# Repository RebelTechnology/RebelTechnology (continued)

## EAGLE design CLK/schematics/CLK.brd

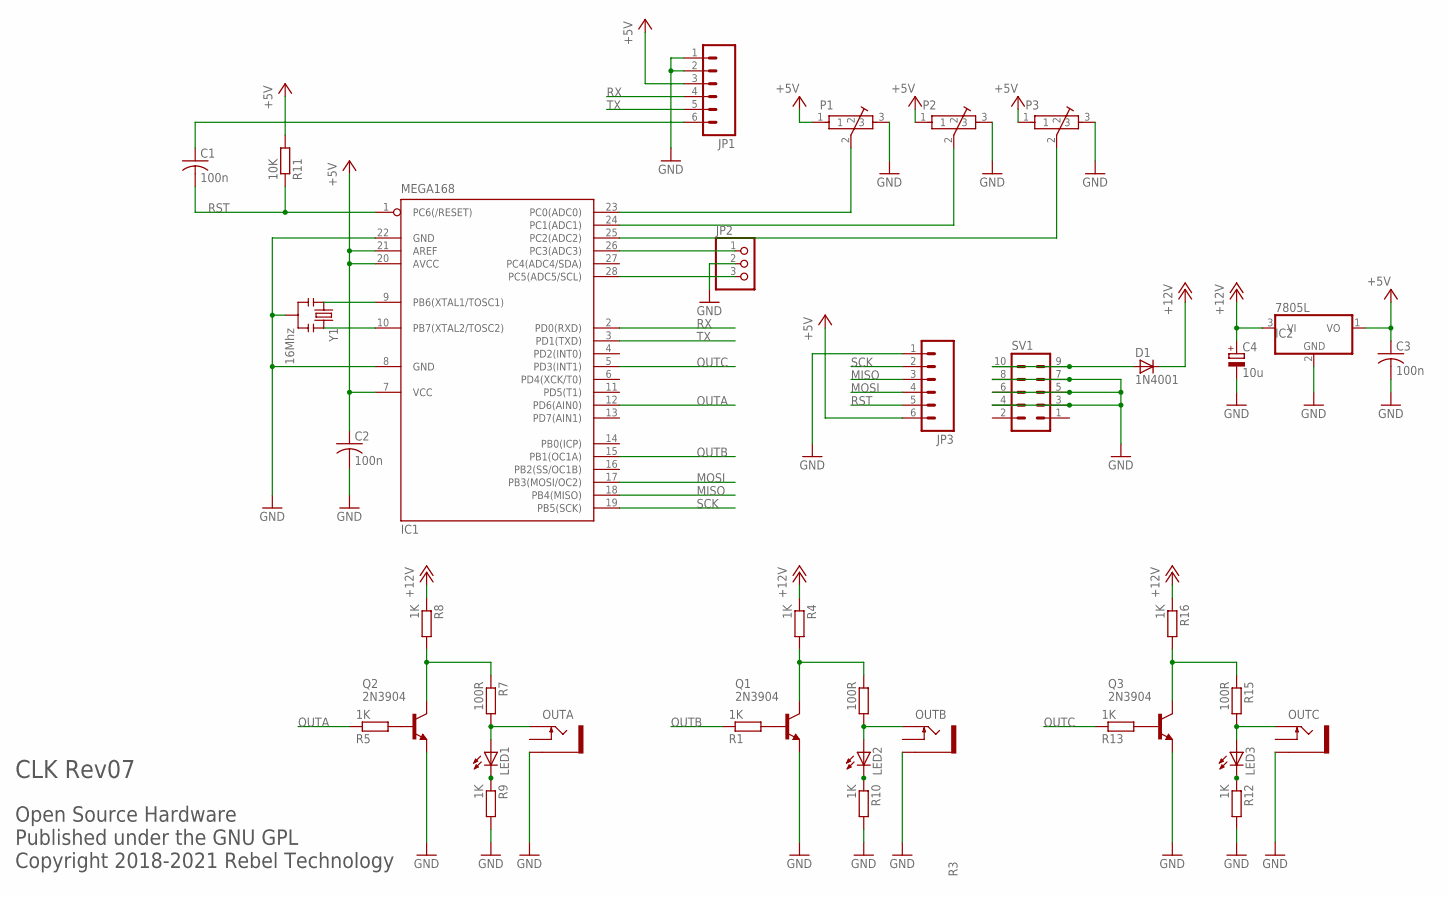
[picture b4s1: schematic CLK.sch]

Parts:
C1, C2, C3: 100n; C050-024X044
C4: 10u; E5-6
D1: 1N4001; DIODE-1N4001
IC1: MEGA168; DIL28-3
IC2: 7805L; TO92
JP1, JP3: M06SIP; 1X06
JP2: PINHD-1X3; 1X03
LED1, LED2, LED3: LED3MM
OUTA: PJ302M
OUTB: PJ302M
OUTC: PJ302M
P1, P2, P3: POT-BOURNS-PTD901
Q1, Q2, Q3: 2N3904; TO92
R1, R4, R5, R8, R9, R10, R12, R13, R16: 1K; 0204/7
R3, R7, R15: 100R; 0204/7
R11: 10K; 0204/7
SV1: MA05-2
Y1: 16Mhz; RESONATOR-PTH

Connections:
+5V: C2.1, C3.1, IC1.7 (VCC), IC1.20 (AVCC), IC1.21 (AREF), IC2.1 (VO), JP1.3, JP3.6, P1.1, P2.1, P3.1, R11.2
+12V: C4.+, D1.C, IC2.3 (VI), R4.1, R8.1, R16.1
ADC0: IC1.23 (PC0(ADC0)), P1.2
ADC1: IC1.24 (PC1(ADC1)), P2.2
ADC2: IC1.25 (PC2(ADC2)), P3.2
GND: C2.2, C3.2, C4.-, IC1.8 (GND), IC1.22 (GND), IC2.2 (GND), JP1.1, JP1.2, JP2.2, JP3.1, OUTA.GND (SLEEVE), OUTB.GND (SLEEVE), OUTC.GND (SLEEVE), P1.3, P2.3, P3.3, Q1.3 (E), Q2.3 (E), Q3.3 (E), R9.2, R10.2, R12.2, SV1.3, SV1.4, SV1.5, SV1.6, SV1.7, SV1.8, Y1.2
MISO: IC1.18 (PB4(MISO)), JP3.3
MOSI: IC1.17 (PB3(MOSI/OC2)), JP3.4
unnamed: LED3.K (C), R12.1
unnamed: IC1.9 (PB6(XTAL1/TOSC1)), Y1.1
unnamed: IC1.10 (PB7(XTAL2/TOSC2)), Y1.3
unnamed: IC1.28 (PC5(ADC5/SCL)), JP2.3
unnamed: LED2.A, OUTB.TIP, R3.2
unnamed: Q1.1 (C), R3.1, R4.2
unnamed: IC1.26 (PC3(ADC3)), JP2.1
unnamed: Q1.2 (B), R1.2
unnamed: Q3.2 (B), R13.2
unnamed: LED3.A, OUTC.TIP, R15.2
unnamed: Q3.1 (C), R15.1, R16.2
unnamed: Q2.2 (B), R5.2
unnamed: LED1.A, OUTA.TIP, R7.2
unnamed: Q2.1 (C), R7.1, R8.2
unnamed: LED1.K (C), R9.1
unnamed: C1.1, JP1.6
unnamed: LED2.K (C), R10.1
unnamed: D1.A, SV1.9, SV1.10
OUTA: IC1.12 (PD6(AIN0)), R5.1
OUTB: IC1.15 (PB1(OC1A)), R1.1
OUTC: IC1.5 (PD3(INT1)), R13.1
RST: C1.2, IC1.1 (PC6(/RESET)), JP3.5, R11.1
RX: IC1.2 (PD0(RXD)), JP1.4
SCK: IC1.19 (PB5(SCK)), JP3.2
TX: IC1.3 (PD1(TXD)), JP1.5

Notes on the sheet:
Open Source Hardware Published under the GNU GPL Copyright 2018-2021 Rebel Technology
CLK Rev07

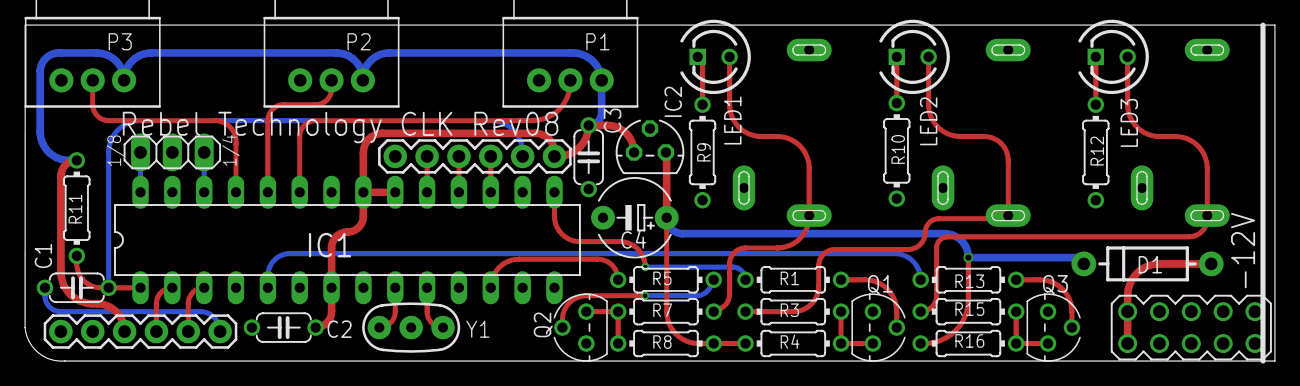
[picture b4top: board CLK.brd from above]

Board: 2 copper layers, 99.7 x 26.8 mm, 37 parts (0 on the bottom side), 33 nets.

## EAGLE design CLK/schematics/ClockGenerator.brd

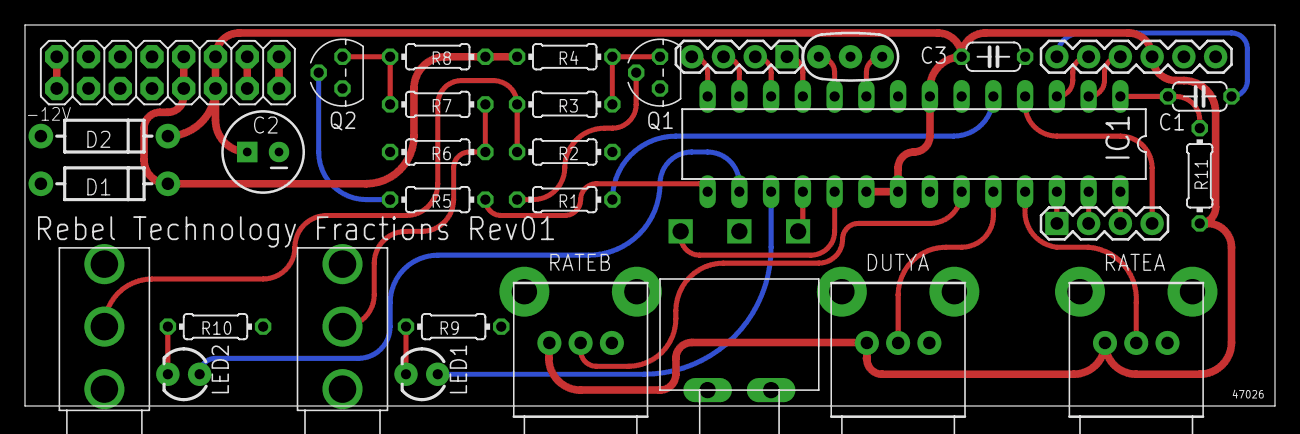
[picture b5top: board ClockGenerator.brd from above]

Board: 2 copper layers, 100.0 x 30.5 mm, 32 parts (0 on the bottom side), 37 nets.

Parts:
C1, C3: 100n; C050-024X044
C2: 100u; CPOL-RADIAL-100UF-25V
D1, D2: DIODE-1N4001
DUTYA: POT-ALPS_RK09L; POT-ALPS_RK09L1120
IC1: MEGA168; DIL28-3
JP1: 1X06
JP2, JP3: 1X04
LED1, LED2: LED3MM
OUTA: JACK-UJ-3502-R; UJ-3502-R
OUTB: JACK-UJ-3502-R; UJ-3502-R
Q1, Q2: 2N3904; TO92
R1, R2, R4, R5, R6, R8, R9, R10: 1K; 0204/7
R3, R7: 100; 0204/7
R11: 10K; 0204/7
RATEA: POT-ALPS_RK09L; POT-ALPS_RK09L1120
RATEB: POT-ALPS_RK09L; POT-ALPS_RK09L1120
SW1: SWITCH-TOGGLE; SWITCH-SPDT-SALECOM-T8020
U$2: M08X2; 2X8
Y1: 16Mhz; RESONATOR-PTH

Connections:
+5V: C2.1, C3.1, D2.C, DUTYA.1, IC1.7, IC1.20, IC1.21, JP1.3, R11.2, RATEA.1, RATEB.1, U$2.11, U$2.12
+12V: D1.C, R4.1, R8.1, U$2.9, U$2.10
ADC0: IC1.23, RATEB.2
ADC1: DUTYA.2, IC1.24
ADC2: IC1.25, RATEA.2
GND: C2.2, C3.2, D1.A, D2.A, DUTYA.3, DUTYA.SHLD1, DUTYA.SHLD2, IC1.8, IC1.22, JP1.1, JP1.2, OUTA.P$3, OUTB.P$3, Q1.3, Q2.3, R2.1, R6.1, R9.2, R10.2, RATEA.3, RATEA.SHLD1, RATEA.SHLD2, RATEB.3, RATEB.SHLD1, RATEB.SHLD2, SW1.2, U$2.3, U$2.4, U$2.5, U$2.6, U$2.7, U$2.8, Y1.2
unnamed: IC1.19, SW1.1
unnamed: IC1.11, JP2.1
unnamed: IC1.16, LED2.A
unnamed: IC1.9, Y1.1
unnamed: IC1.10, Y1.3
unnamed: IC1.17, LED1.A
unnamed: IC1.4, JP3.4
unnamed: IC1.28, JP3.3
unnamed: IC1.27, JP3.2
unnamed: OUTB.P$1, R2.2, R3.2
unnamed: Q1.1, R3.1, R4.2
unnamed: IC1.26, JP3.1
unnamed: IC1.12, JP2.2
unnamed: IC1.13, JP2.3
unnamed: U$2.13, U$2.14
unnamed: IC1.14, JP2.4
unnamed: IC1.18, SW1.3
unnamed: Q1.2, R1.2
unnamed: Q2.2, R5.2
unnamed: OUTA.P$1, R6.2, R7.2
unnamed: Q2.1, R7.1, R8.2
unnamed: LED1.K, R9.1
unnamed: C1.1, JP1.6
unnamed: LED2.K, R10.1
unnamed: C1.2, IC1.1, R11.1
OUTA: IC1.15, R5.1
OUTB: IC1.5, R1.1
PWR_BUS: U$2.15, U$2.16
RX: IC1.2, JP1.4
TX: IC1.3, JP1.5
V-: U$2.1, U$2.2

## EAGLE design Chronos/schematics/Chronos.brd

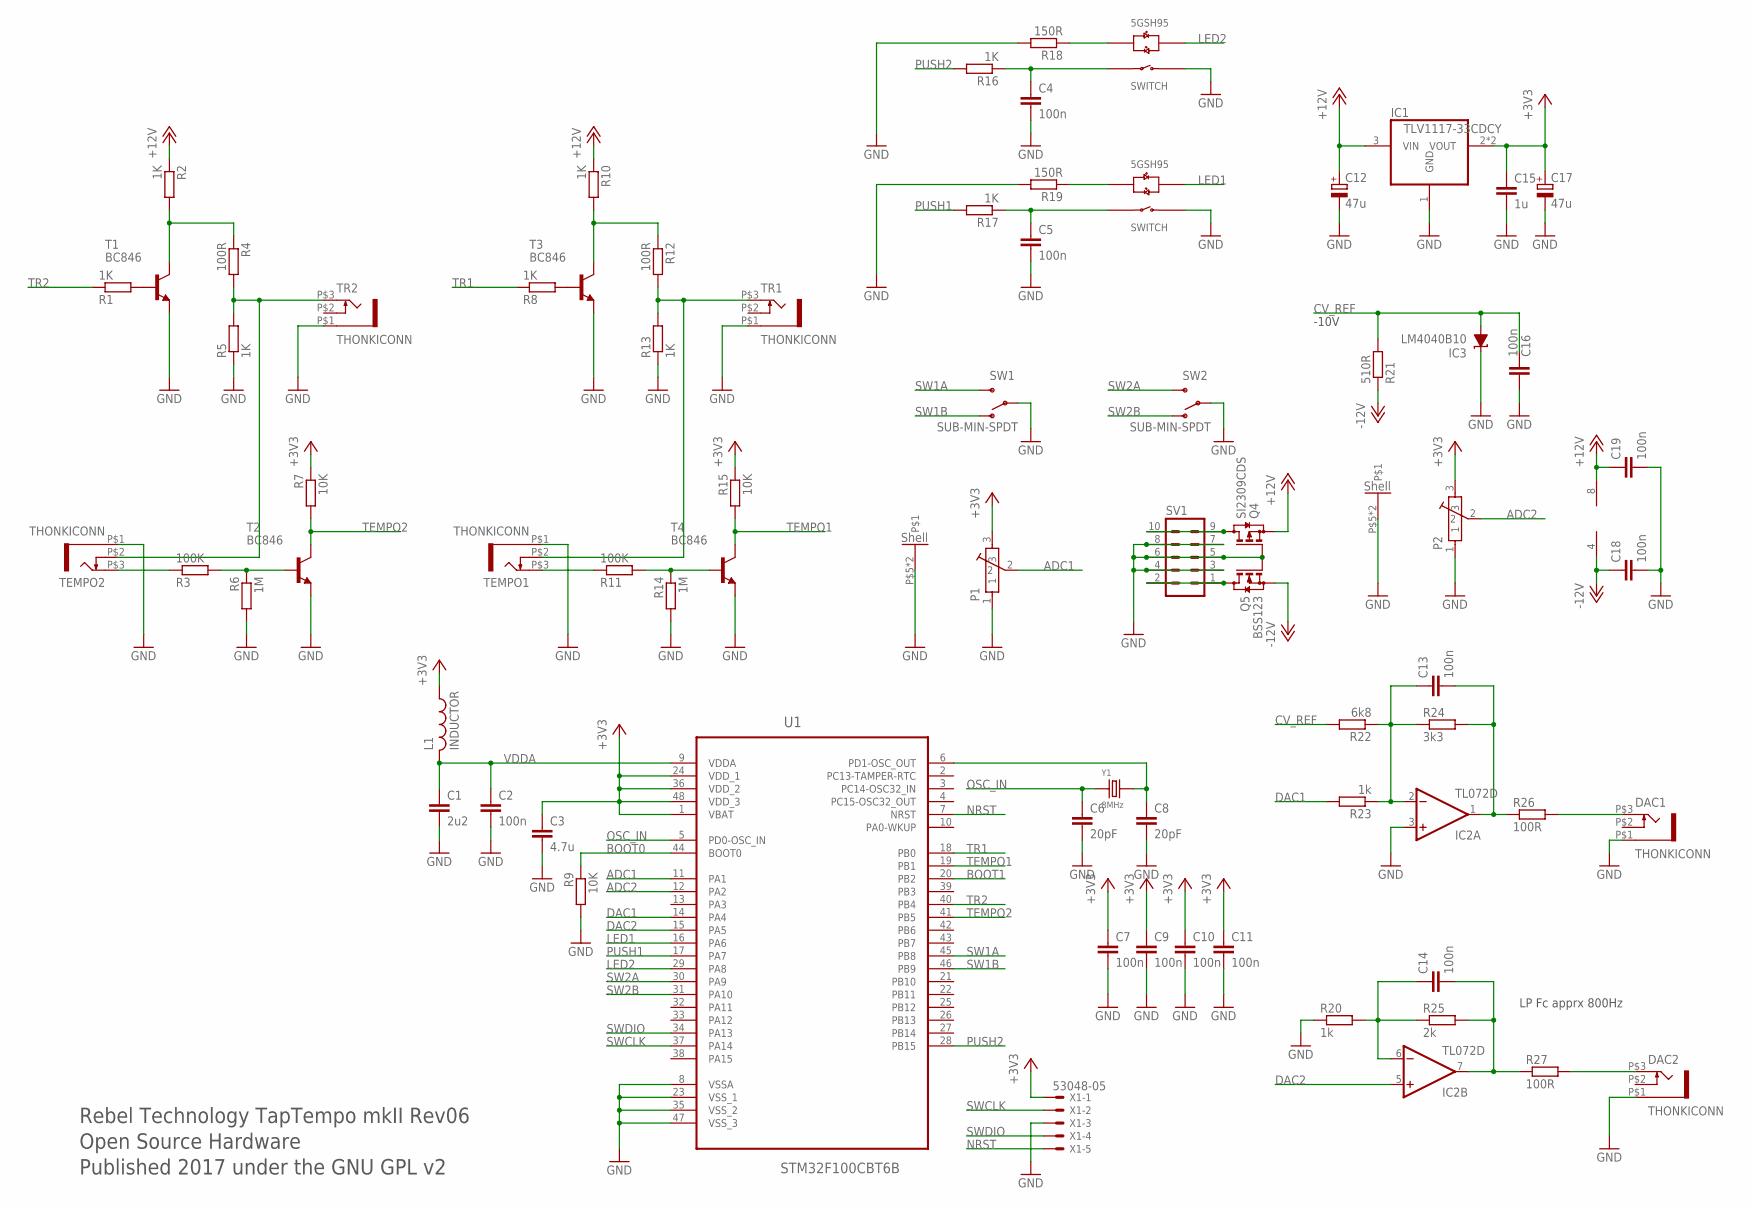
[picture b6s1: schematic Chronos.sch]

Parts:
C1: 2u2; C0603
C2, C4, C5, C7, C9, C10, C11, C13, C14, C16, C18, C19: 100n; C0603
C3: 4.7u; C0603
C6, C8: 20pF; C0603
C12, C17: 47u; CPOL-5; FARNELL 882-3014
C15: 1u; C0603
DAC1, DAC2: THONKICONN
IC1: TLV1117-33CDCY; SOT223; FARNELL 149-4942
IC2: TL072D; SO08
IC3: LM4040B10; DBZ_R-PDSO-G3
L1: INDUCTOR; 0603
P1, P2: POT-ALPS-RK09L1140
PUSH1, PUSH2: 5GTH9
Q4: SI2309CDS; SOT23
Q5: BSS123; SOT23
R1, R2, R5, R8, R10, R13, R16, R17: 1K; 0603
R3, R11: 100K; 0603
R4, R12, R26, R27: 100R; 0603
R6, R14: 1M; 0603
R7, R9, R15: 10K; 0603
R18, R19: 150R; 0603
R20, R23: 1k; 0603
R21: 510R; 0603
R22: 6k8; 0603
R24: 3k3; 0603
R25: 2k; 0603
SV1: MA05-2
SW1, SW2: SUB-MIN-SPDT
T1, T2, T3, T4: BC846; SOT23
TEMPO1, TEMPO2: THONKICONN
TR1, TR2: THONKICONN
U1: STM32F100CBT6B; QFP50P900X900X160-48N
X1: 53048-05
Y1: 8MHz; X2-SMD-5.0X3.2X1.3MM

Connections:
+3V3: C3.1, C7.1, C9.1, C10.1, C11.1, C15.1, C17.+, IC1.2 (VOUT), IC1.4 (VOUT), L1.1, P1.3, P2.3, R7.1, R15.1, U1.1 (VBAT), U1.24 (VDD_1), U1.36 (VDD_2), U1.48 (VDD_3), X1.1
+12V: C12.+, C19.1, IC1.3 (VIN), IC2.8 (V+), Q4.2 (S), R2.1, R10.1
-12V: C18.1, IC2.4 (V-), Q5.2 (S), R21.1
ADC1: P1.2, U1.11 (PA1)
ADC2: P2.2, U1.12 (PA2)
BOOT0: R9.1, U1.44 (BOOT0)
BOOT1: U1.20 (PB2)
CV_REF: C16.1, IC3.2 (A), R21.2, R22.2
DAC1: R23.2, U1.14 (PA4)
DAC2: IC2.5 (+IN), U1.15 (PA5)
GND: C1.2, C2.2, C3.2, C4.2, C5.2, C6.2, C7.2, C8.2, C9.2, C10.2, C11.2, C12.-, C15.2, C16.2, C17.-, C18.2, C19.2, DAC1.P$1 (5), DAC2.P$1 (5), IC1.1 (GND), IC2.3 (+IN), IC3.1 (C), P1.1, P1.P$5, P1.P$6, P2.1, P2.P$5, P2.P$6, PUSH1.1 (SWITCH_B), PUSH2.1 (SWITCH_B), Q4.1 (G), Q5.1 (G), R5.1, R6.2, R9.2, R13.1, R14.2, R18.2, R19.2, R20.1, SV1.3, SV1.4, SV1.5, SV1.6, SV1.7, SV1.8, SW1.2, SW2.2, T1.2 (E), T2.2 (E), T3.2 (E), T4.2 (E), TEMPO1.P$1 (5), TEMPO2.P$1 (5), TR1.P$1 (5), TR2.P$1 (5), U1.8 (VSSA), U1.23 (VSS_1), U1.35 (VSS_2), U1.47 (VSS_3), X1.3
LED1: PUSH1.+3 (LED_R+), U1.16 (PA6)
LED2: PUSH2.+3 (LED_R+), U1.29 (PA8)
unnamed: C8.1, U1.6 (PD1-OSC_OUT), Y1.2
unnamed: PUSH1.-2 (LED_G+), R19.1
unnamed: C14.2, IC2.7 (OUT), R25.2, R27.1
unnamed: C14.1, IC2.6 (-IN), R20.2, R25.1
unnamed: R12.2, R13.2, TEMPO1.P$2 (4), TR1.P$3 (3)
unnamed: Q4.3 (D), SV1.9, SV1.10
unnamed: C13.2, IC2.1 (OUT), R24.2, R26.1
unnamed: PUSH2.-2 (LED_G+), R18.1
unnamed: R3.2, R6.1, T2.1 (B)
unnamed: R1.2, T1.1 (B)
unnamed: R2.2, R4.1, T1.3 (C)
unnamed: C13.1, IC2.2 (-IN), R22.1, R23.1, R24.1
unnamed: R3.1, TEMPO2.P$3 (3)
unnamed: R4.2, R5.2, TEMPO2.P$2 (4), TR2.P$3 (3)
unnamed: Q5.3 (D), SV1.1, SV1.2
unnamed: C5.1, PUSH1.4 (SWITCH_A), R17.1
unnamed: C4.1, PUSH2.4 (SWITCH_A), R16.1
unnamed: R11.1, TEMPO1.P$3 (3)
unnamed: R11.2, R14.1, T4.1 (B)
unnamed: DAC1.P$3 (3), R26.2
unnamed: DAC2.P$3 (3), R27.2
unnamed: R8.2, T3.1 (B)
unnamed: R10.2, R12.1, T3.3 (C)
NRST: U1.7 (NRST), X1.5
OSC_IN: C6.1, U1.5 (PD0-OSC_IN), Y1.1
PUSH1: R17.2, U1.17 (PA7)
PUSH2: R16.2, U1.28 (PB15)
SW1A: SW1.3 (S), U1.45 (PB8)
SW1B: SW1.1 (O), U1.46 (PB9)
SW2A: SW2.3 (S), U1.30 (PA9)
SW2B: SW2.1 (O), U1.31 (PA10)
SWCLK: U1.37 (PA14), X1.2
SWDIO: U1.34 (PA13), X1.4
TEMPO1: R15.2, T4.3 (C), U1.19 (PB1)
TEMPO2: R7.2, T2.3 (C), U1.41 (PB5)
TR1: R8.1, U1.18 (PB0)
TR2: R1.1, U1.40 (PB4)
VDDA: C1.1, C2.1, L1.2, U1.9 (VDDA)

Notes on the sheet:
Rebel Technology TapTempo mkII Rev06
Published 2017 under the GNU GPL v2
LP Fc apprx 800Hz
-10V
Open Source Hardware

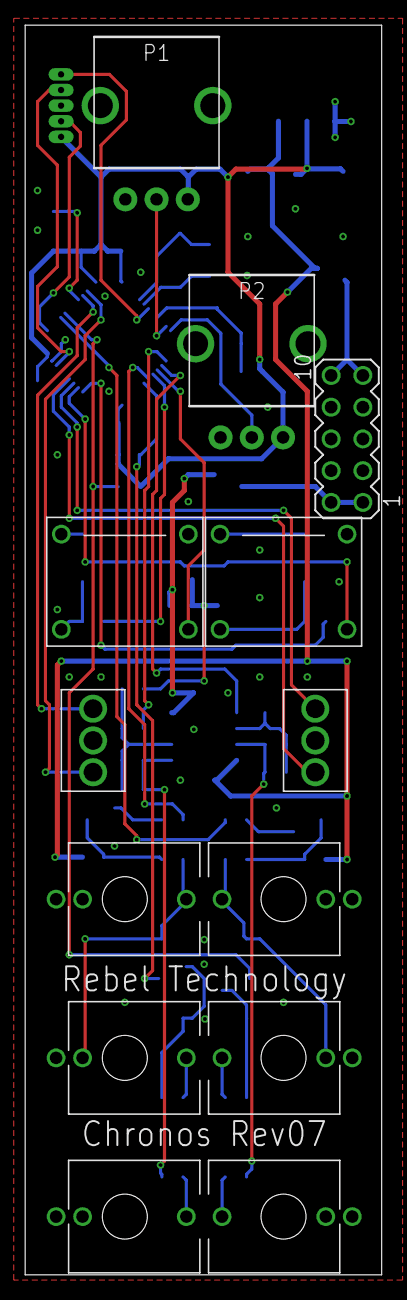
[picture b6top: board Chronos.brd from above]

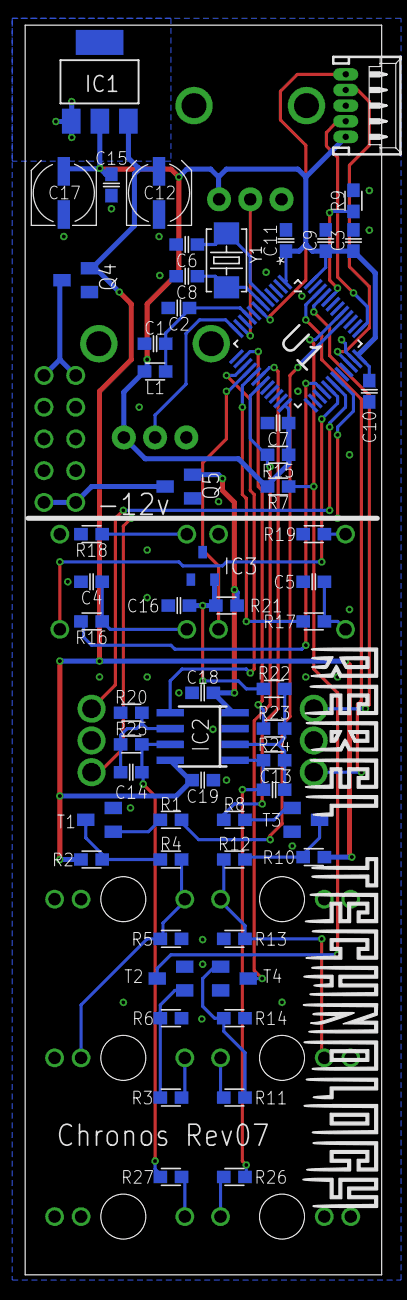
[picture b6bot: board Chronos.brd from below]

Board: 2 copper layers, 28.5 x 100.0 mm, 72 parts (59 on the bottom side), 50 nets.

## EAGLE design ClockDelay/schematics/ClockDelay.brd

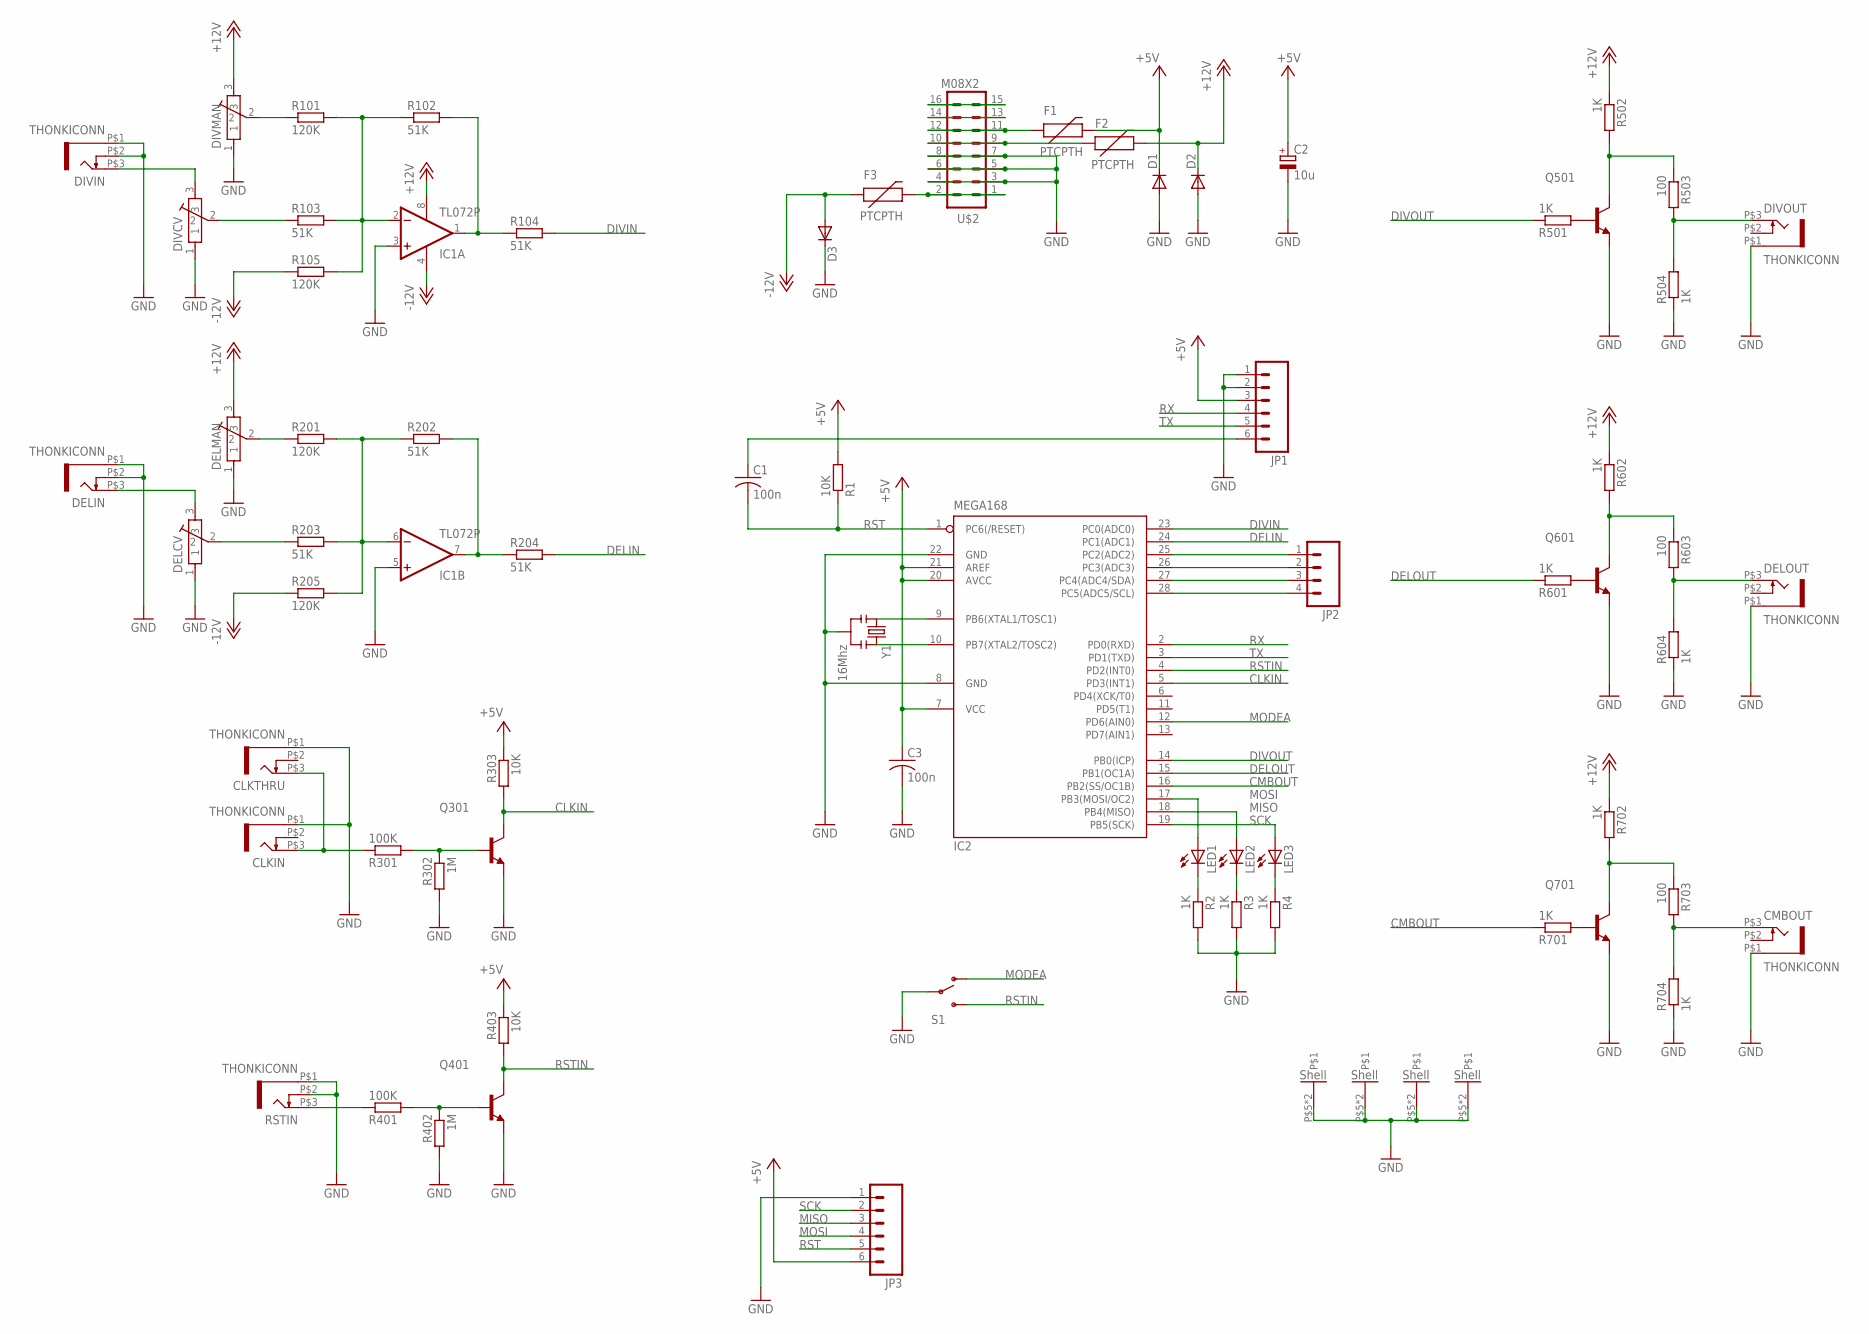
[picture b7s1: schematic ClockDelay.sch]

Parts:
C1, C3: 100n; C050-024X044
C2: 10u; E5-6
CLKIN: THONKICONN
CLKTHRU: THONKICONN
CMBOUT: THONKICONN
D1, D2, D3: DIODE1N4001; DIODE-1N4001
DELCV: POT-ALPS-RK09L1140
DELIN: THONKICONN
DELMAN: POT-ALPS-RK09L1140
DELOUT: THONKICONN
DIVCV: POT-ALPS-RK09L1140
DIVIN: THONKICONN
DIVMAN: POT-ALPS-RK09L1140
DIVOUT: THONKICONN
F1, F2, F3: PTCPTH; PTC
IC1: TL072P; DIL08
IC2: MEGA168; DIL28-3
JP1, JP3: M06SIP; 1X06
JP2: M04PTH; 1X04
LED1, LED2, LED3: LED3MM
Q301, Q401, Q501, Q601, Q701: 2N3904-NPN-TO92-EBC; TO92-EBC
R1, R303, R403: 10K; 0204/7
R2, R3, R4, R501, R502, R504, R601, R602, R604, R701, R702, R704: 1K; 0204/7
R101, R105, R201, R205: 120K; 0204/7
R102, R103, R104, R202, R203, R204: 51K; 0204/7
R301, R401: 100K; 0204/7
R302, R402: 1M; 0204/7
R503, R603, R703: 100; 0204/7
RSTIN: THONKICONN
S1: SWITCH-SPST; SWITCH-SPDT-SALECOM-T8014
U$2: M08X2; 2X8
Y1: 16Mhz; RESONATOR-PTH

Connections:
+5V: C2.+, C3.1, D1.C, F1.P$2 (2), IC2.7 (VCC), IC2.20 (AVCC), IC2.21 (AREF), JP1.3, JP3.6, R1.2, R303.1, R403.1
+12V: D2.C, DELMAN.3, DIVMAN.3, F2.P$2 (2), IC1.8 (V+), R502.1, R602.1, R702.1
-12V: D3.A, F3.P$1 (1), IC1.4 (V-), R105.1, R205.1
CLKIN: IC2.5 (PD3(INT1)), Q301.C, R303.2
CMBOUT: IC2.16 (PB2(SS/OC1B)), R701.1
DELIN: IC2.24 (PC1(ADC1)), R204.2
DELOUT: IC2.15 (PB1(OC1A)), R601.1
DIVIN: IC2.23 (PC0(ADC0)), R104.2
DIVOUT: IC2.14 (PB0(ICP)), R501.1
GND: C2.-, C3.2, CLKIN.P$1 (5), CLKTHRU.P$1 (5), CMBOUT.P$1 (5), D1.A, D2.A, D3.C, DELCV.1, DELCV.P$5, DELCV.P$6, DELIN.P$1 (5), DELIN.P$2 (4), DELMAN.1, DELMAN.P$5, DELMAN.P$6, DELOUT.P$1 (5), DIVCV.1, DIVCV.P$5, DIVCV.P$6, DIVIN.P$1 (5), DIVIN.P$2 (4), DIVMAN.1, DIVMAN.P$5, DIVMAN.P$6, DIVOUT.P$1 (5), IC1.3 (+IN), IC1.5 (+IN), IC2.8 (GND), IC2.22 (GND), JP1.1, JP1.2, JP3.1, Q301.E, Q401.E, Q501.E, Q601.E, Q701.E, R2.2, R3.2, R4.2, R302.2, R402.2, R504.1, R604.1, R704.1, RSTIN.P$1 (5), RSTIN.P$2 (4), S1.2, U$2.3, U$2.4, U$2.5, U$2.6, U$2.7, U$2.8, Y1.2
MISO: IC2.18 (PB4(MISO)), JP3.3, LED2.A
MODEA: IC2.12 (PD6(AIN0)), S1.1 (O)
MOSI: IC2.17 (PB3(MOSI/OC2)), JP3.4, LED1.A
unnamed: DIVCV.3, DIVIN.P$3 (3)
unnamed: IC1.2 (-IN), R101.2, R102.1, R103.2, R105.2
unnamed: DIVMAN.2, R101.1
unnamed: IC1.1 (OUT), R102.2, R104.1
unnamed: DIVCV.2, R103.1
unnamed: F3.P$2 (2), U$2.1, U$2.2
unnamed: IC1.6 (-IN), R201.2, R202.1, R203.2, R205.2
unnamed: DELMAN.2, R201.1
unnamed: IC1.7 (OUT), R202.2, R204.1
unnamed: DELCV.2, R203.1
unnamed: IC2.25 (PC2(ADC2)), JP2.1
unnamed: DELCV.3, DELIN.P$3 (3)
unnamed: IC2.26 (PC3(ADC3)), JP2.2
unnamed: IC2.27 (PC4(ADC4/SDA)), JP2.3
unnamed: IC2.28 (PC5(ADC5/SCL)), JP2.4
unnamed: IC2.9 (PB6(XTAL1/TOSC1)), Y1.1
unnamed: IC2.10 (PB7(XTAL2/TOSC2)), Y1.3
unnamed: LED1.K (C), R2.1
unnamed: LED2.K (C), R3.1
unnamed: LED3.K (C), R4.1
unnamed: Q601.B, R601.2
unnamed: Q301.B, R301.2, R302.1
unnamed: CLKIN.P$3 (3), CLKTHRU.P$3 (3), R301.1
unnamed: C1.1, JP1.6
unnamed: DELOUT.P$3 (3), R603.2, R604.2
unnamed: Q401.B, R401.2, R402.1
unnamed: Q601.C, R602.2, R603.1
unnamed: Q501.B, R501.2
unnamed: Q701.B, R701.2
unnamed: CMBOUT.P$3 (3), R703.2, R704.2
unnamed: DIVOUT.P$3 (3), R503.2, R504.2
unnamed: Q501.C, R502.2, R503.1
unnamed: Q701.C, R702.2, R703.1
unnamed: R401.1, RSTIN.P$3 (3)
unnamed: U$2.13, U$2.14
unnamed: F1.P$1 (1), U$2.11, U$2.12
unnamed: F2.P$1 (1), U$2.9, U$2.10
PWR_BUS: U$2.15, U$2.16
RST: C1.2, IC2.1 (PC6(/RESET)), JP3.5, R1.1
RSTIN: IC2.4 (PD2(INT0)), Q401.C, R403.2, S1.3 (S)
RX: IC2.2 (PD0(RXD)), JP1.4
SCK: IC2.19 (PB5(SCK)), JP3.2, LED3.A
TX: IC2.3 (PD1(TXD)), JP1.5

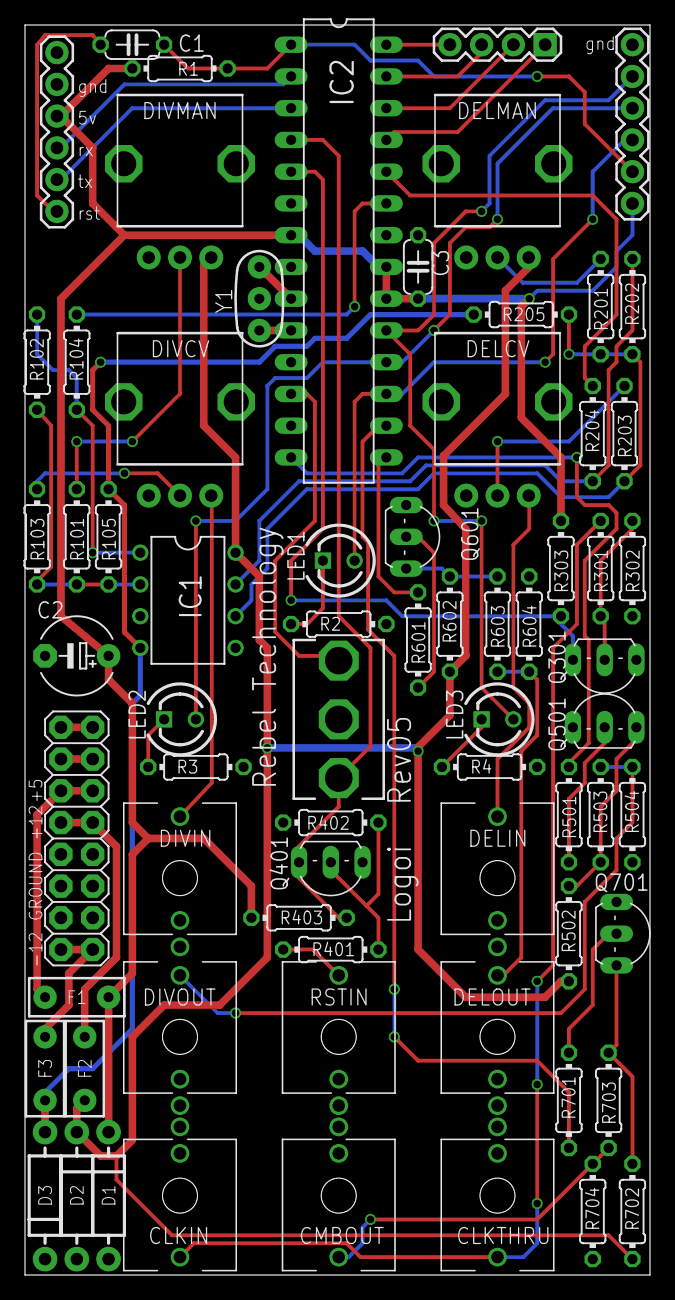
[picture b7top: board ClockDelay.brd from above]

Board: 2 copper layers, 50.0 x 100.0 mm, 69 parts (0 on the bottom side), 56 nets.
